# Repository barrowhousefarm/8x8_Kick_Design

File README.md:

# 8x8 Kick_Design
 8x8 Kick Drum Docs
 Any errors are mine.. and you can copy or correct them!

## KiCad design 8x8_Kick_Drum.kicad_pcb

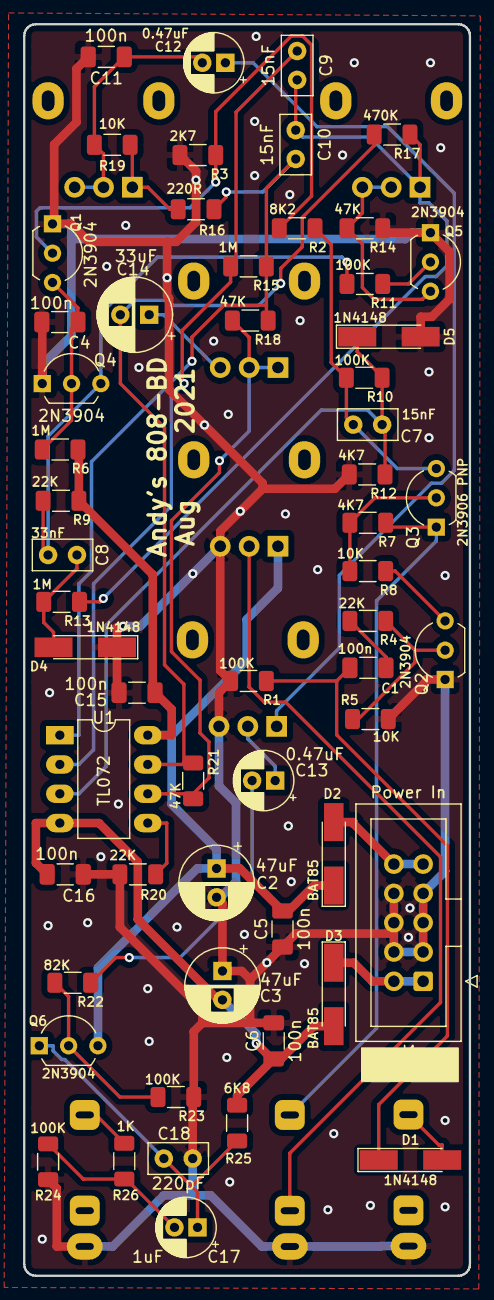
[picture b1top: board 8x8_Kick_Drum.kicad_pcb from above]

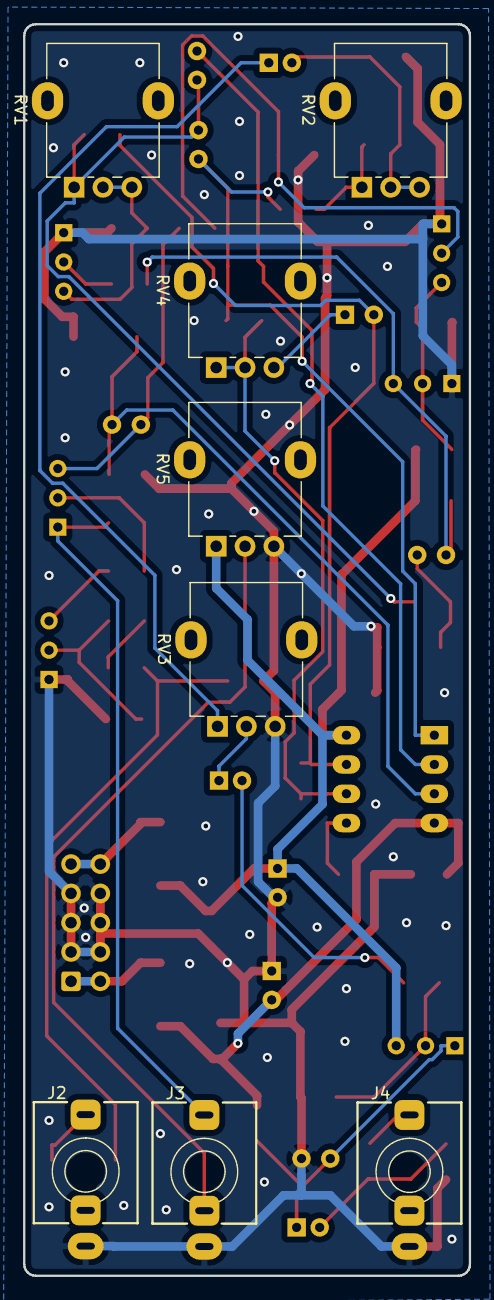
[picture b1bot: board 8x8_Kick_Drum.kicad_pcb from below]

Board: 2 copper layers, 38.6 x 108.5 mm, 65 parts (8 on the bottom side), 37 nets.

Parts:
C1, C4, C5, C6, C11, C15, C16: 100n; C_1206_3216Metric_Pad1.33x1.80mm_HandSolder
C2, C3: 47uF; CP_Radial_D6.3mm_P2.50mm
C7, C9, C10: 15nF; C_Disc_D5.0mm_W2.5mm_P2.50mm
C8: 33nF; C_Disc_D5.0mm_W2.5mm_P2.50mm
C12, C13: 0.47uF; CP_Radial_D5.0mm_P2.00mm
C14: 33uF; CP_Radial_D6.3mm_P2.50mm
C17: 1uF; CP_Radial_D5.0mm_P2.00mm
C18: 220pF; C_Disc_D5.0mm_W2.5mm_P2.50mm
D1, D4, D5: 1N4148; D_MiniMELF_Handsoldering
D2, D3: BAT85; D_MiniMELF_Handsoldering
J1: Power In; IDC-Header_2x05_P2.54mm_Vertical
J2: BD_Trig; Jack_3.5mm_QingPu_WQP-PJ398SM_Vertical
J3: Accent_In; Jack_3.5mm_QingPu_WQP-PJ398SM_Vertical
J4: BD_Out; Jack_3.5mm_QingPu_WQP-PJ398SM_Vertical
Q1, Q2, Q4, Q5, Q6: 2N3904; TO-92L_Inline_Wide
Q3: 2N3906 PNP; TO-92L_Inline_Wide
R1, R10, R11, R23, R24: 100K; R_1206_3216Metric_Pad1.30x1.75mm_HandSolder
R2: 8K2; R_1206_3216Metric_Pad1.30x1.75mm_HandSolder
R3: 2K7; R_1206_3216Metric_Pad1.30x1.75mm_HandSolder
R4, R9, R20: 22K; R_1206_3216Metric_Pad1.30x1.75mm_HandSolder
R5, R8, R19: 10K; R_1206_3216Metric_Pad1.30x1.75mm_HandSolder
R6, R13, R15: 1M; R_1206_3216Metric_Pad1.30x1.75mm_HandSolder
R7, R12: 4K7; R_1206_3216Metric_Pad1.30x1.75mm_HandSolder
R14, R18, R21: 47K; R_1206_3216Metric_Pad1.30x1.75mm_HandSolder
R16: 220R; R_1206_3216Metric_Pad1.30x1.75mm_HandSolder
R17: 470K; R_1206_3216Metric_Pad1.30x1.75mm_HandSolder
R22: 82K; R_1206_3216Metric_Pad1.30x1.75mm_HandSolder
R25: 6K8; R_1206_3216Metric_Pad1.30x1.75mm_HandSolder
R26: 1K; R_1206_3216Metric_Pad1.30x1.75mm_HandSolder
RV1: BD Tune Env 10K; Potentiometer_Alpha_RD901F-40-00D_Single_Vertical
RV2: BD Tone 10K; Potentiometer_Alpha_RD901F-40-00D_Single_Vertical
RV3: BD Level 10K; Potentiometer_Alpha_RD901F-40-00D_Single_Vertical
RV4: BD Decay 500K; Potentiometer_Alpha_RD901F-40-00D_Single_Vertical
RV5: Accent 10K; Potentiometer_Alpha_RD901F-40-00D_Single_Vertical
U1: TL072; DIP-8_W7.62mm_LongPads

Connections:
+12V: C2.1, C5.2, C15.1, D2.1, Q6.3, R6.2, R9.2, RV5.1, U1.8
-12V: C3.2, C6.1, C16.2, D3.2, R25.1, U1.4
ACCENT_IN: J3.T, Q3.1, R7.1
GND: C2.2, C3.1, C4.1, C5.1, C6.2, C11.2, C15.2, C16.1, C18.2, D4.1, D5.2, J1.3, J1.4, J1.5, J1.6, J1.7, J1.8, J2.S, J3.S, J4.S, Q1.1, Q2.1, Q4.1, Q5.1, R1.2, R3.1, R5.2, R12.1, R14.2, R20.2, R23.1, R24.2, RV3.3, RV5.3
KICK_OUT: J4.T, R26.1
KICK_TRIGGER: D1.2, J2.T
unnamed: C1.1, R4.1
unnamed: C1.2, D1.1, R1.1
unnamed: C4.2, Q1.3, Q4.2, R6.1
unnamed: C7.1, D5.1, R10.1, R12.2, U1.3
unnamed: C7.2, Q3.3, R2.2, R10.2
unnamed: C8.1, Q4.3, R9.1, R11.2
unnamed: C8.2, D4.2, R13.2
unnamed: C9.1, R15.2, U1.2
unnamed: C9.2, C10.1, R13.1, R17.2, RV1.1
unnamed: C10.2, R15.1, R16.1, R18.1, U1.1
unnamed: C11.1, C12.2, R19.2, RV2.2, RV2.3
unnamed: C12.1, RV3.1
unnamed: C13.1, RV3.2
unnamed: C13.2, R22.2
unnamed: C14.1, RV4.3
unnamed: C14.2, R17.1, R21.2, U1.7
unnamed: C17.1, C18.1, Q6.1, R25.2
unnamed: C17.2, R24.1, R26.2
unnamed: D2.2, J1.9, J1.10
unnamed: D3.1, J1.1, J1.2
unnamed: J3.TN, RV5.2
unnamed: Q1.2, R2.1, R3.2
unnamed: Q2.2, R4.2, R5.1
unnamed: Q2.3, R8.2
unnamed: Q3.2, R7.2, R8.1
unnamed: Q5.2, R11.1
unnamed: Q5.3, R14.1, RV1.2, RV1.3
unnamed: Q6.2, R22.1, R23.2
unnamed: R16.2, R19.1, RV2.1
unnamed: R18.2, R21.1, RV4.1, RV4.2, U1.6
unnamed: R20.1, U1.5
